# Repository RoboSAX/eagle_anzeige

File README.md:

# eagle_anzeige
Anzeigeelemente für die Masterplatine der Spielfeldsteuerung

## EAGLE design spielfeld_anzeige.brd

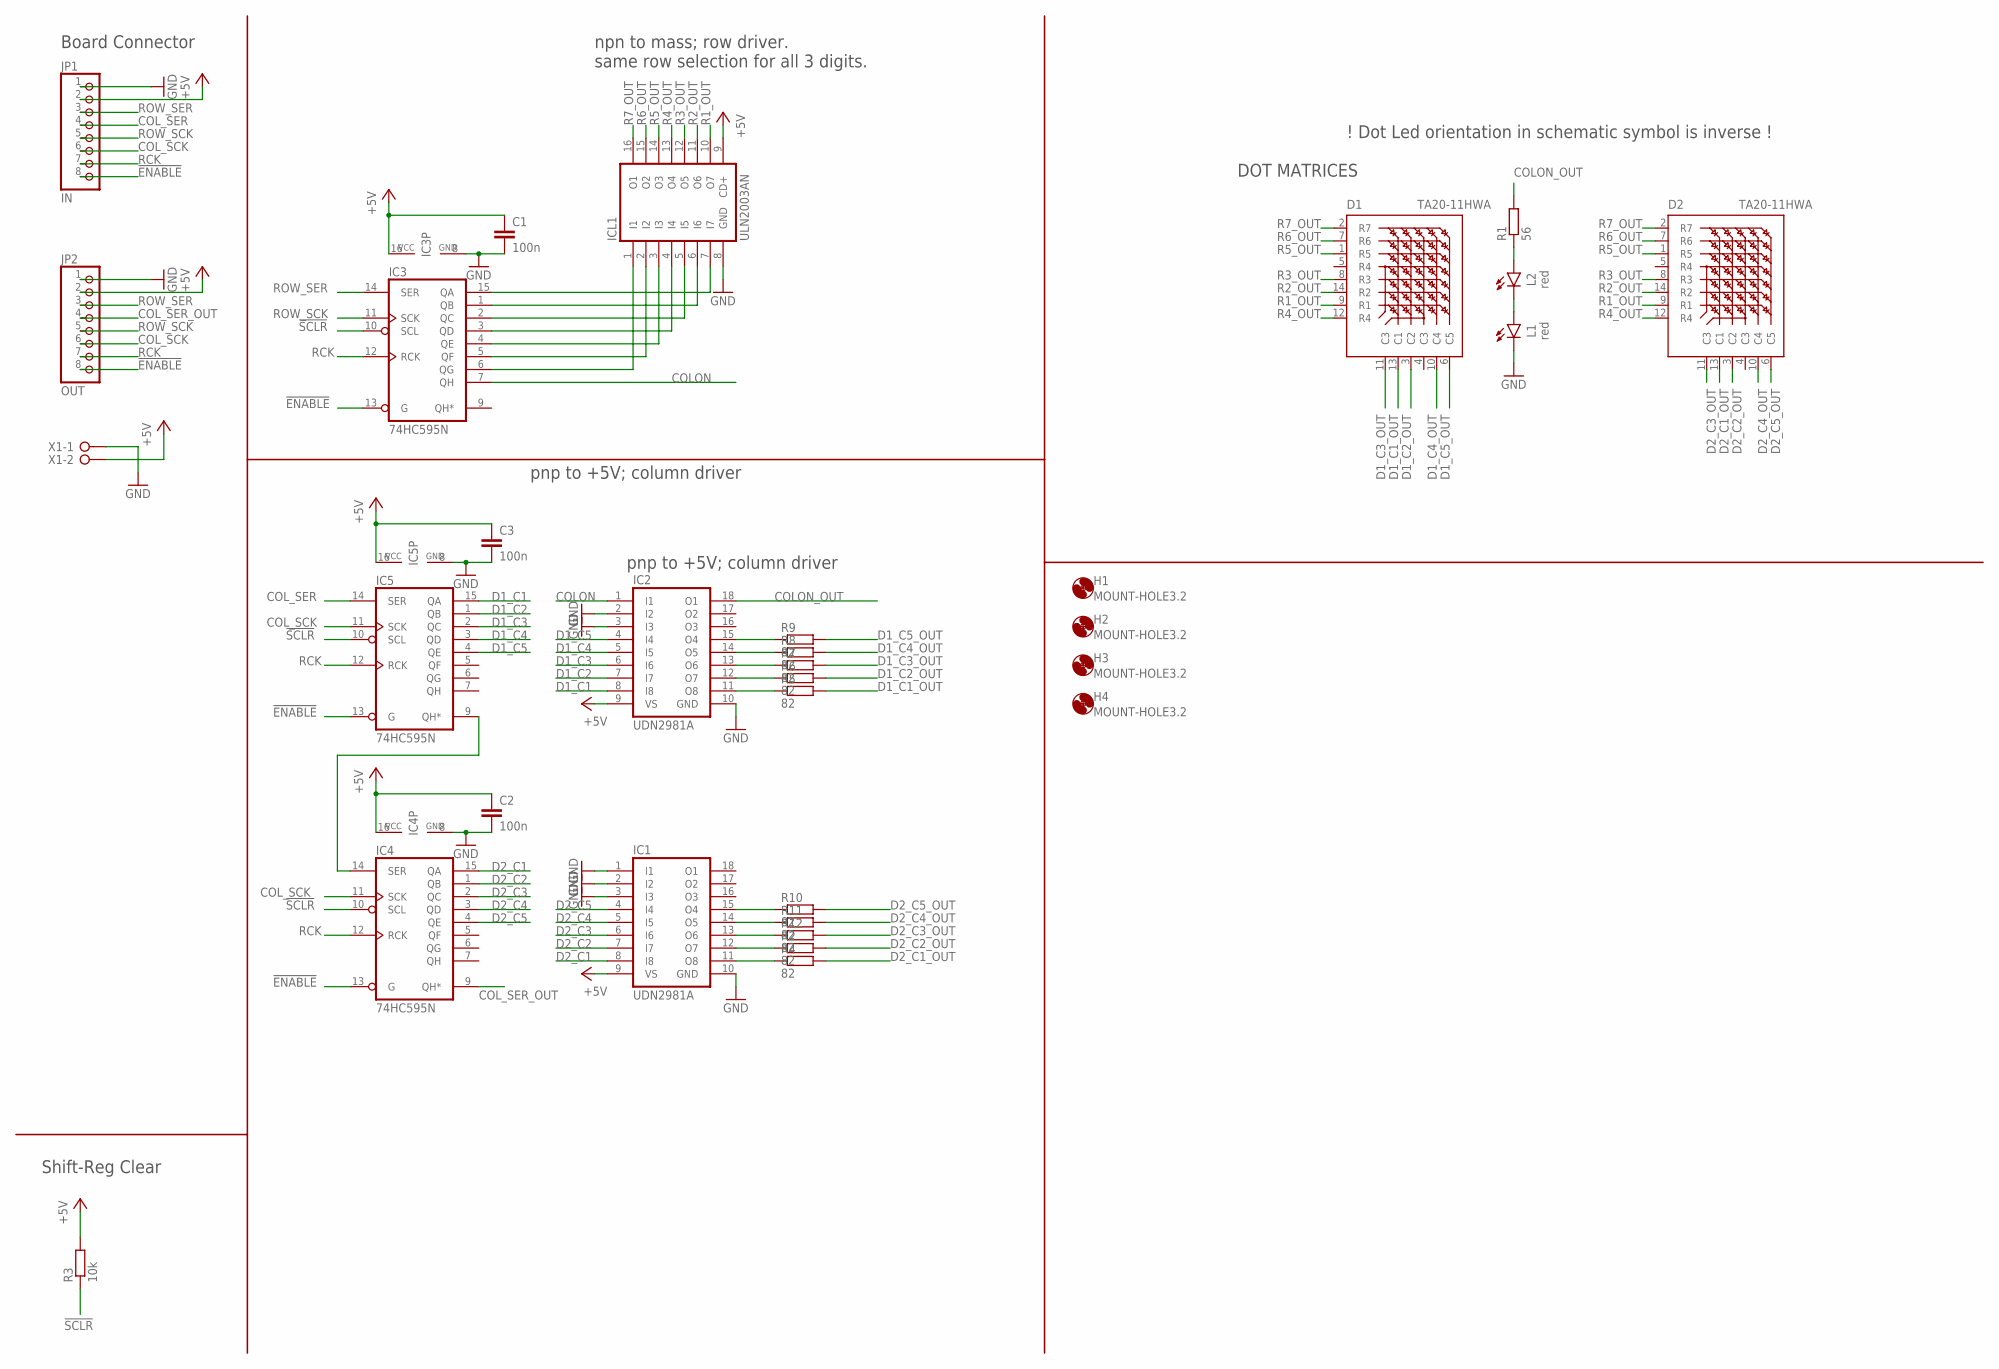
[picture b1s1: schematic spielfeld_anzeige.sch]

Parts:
C1, C2, C3: 100n; C0805
D1, D2: TA20-11HWA
H1, H2, H3, H4: MOUNT-HOLE3.2; 3,2
IC1, IC2: UDN2981A; DIL18
IC3, IC4, IC5: 74HC595N; DIL16
ICL1: ULN2003AN; DIL16
JP1: IN; 1X08
JP2: OUT; 1X08
L1, L2: red; LED_5MM
R1: 56; R3216
R2, R4, R5, R6, R7, R8, R9, R10, R11, R12: 82; R0805
R3: 10k; M3216
X1: W237-02P; W237-132

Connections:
!ENABLE!: IC3.13 (G), IC4.13 (G), IC5.13 (G), JP1.8, JP2.8
!SCLR!: IC3.10 (SCL), IC4.10 (SCL), IC5.10 (SCL), R3.1
+5V: C1.1, C2.1, C3.1, IC1.9 (VS), IC2.9 (VS), IC3.16 (VCC), IC4.16 (VCC), IC5.16 (VCC), ICL1.9 (CD+), JP1.2, JP2.2, R3.2, X1.2
COLON: IC2.1 (I1), IC3.7 (QH)
COLON_OUT: IC2.18 (O1), R1.2
COL_SCK: IC4.11 (SCK), IC5.11 (SCK), JP1.6, JP2.6
COL_SER: IC5.14 (SER), JP1.4
COL_SER_OUT: IC4.9 (QH*), JP2.4
D1_C1: IC2.8 (I8), IC5.15 (QA)
D1_C1_OUT: D1.13 (C1), R5.2
D1_C2: IC2.7 (I7), IC5.1 (QB)
D1_C2_OUT: D1.3 (C2), R6.2
D1_C3: IC2.6 (I6), IC5.2 (QC)
D1_C3_OUT: D1.11 (C3), R7.2
D1_C4: IC2.5 (I5), IC5.3 (QD)
D1_C4_OUT: D1.10 (C4), R8.2
D1_C5: IC2.4 (I4), IC5.4 (QE)
D1_C5_OUT: D1.6 (C5), R9.2
D2_C1: IC1.8 (I8), IC4.15 (QA)
D2_C1_OUT: D2.13 (C1), R4.2
D2_C2: IC1.7 (I7), IC4.1 (QB)
D2_C2_OUT: D2.3 (C2), R2.2
D2_C3: IC1.6 (I6), IC4.2 (QC)
D2_C3_OUT: D2.11 (C3), R12.2
D2_C4: IC1.5 (I5), IC4.3 (QD)
D2_C4_OUT: D2.10 (C4), R11.2
D2_C5: IC1.4 (I4), IC4.4 (QE)
D2_C5_OUT: D2.6 (C5), R10.2
GND: C1.2, C2.2, C3.2, IC1.1 (I1), IC1.2 (I2), IC1.3 (I3), IC1.10 (GND), IC2.2 (I2), IC2.3 (I3), IC2.10 (GND), IC3.8 (GND), IC4.8 (GND), IC5.8 (GND), ICL1.8 (GND), JP1.1, JP2.1, L1.K (C), X1.1
unnamed: L1.A, L2.K (C)
unnamed: IC2.11 (O8), R5.1
unnamed: IC2.12 (O7), R6.1
unnamed: IC2.13 (O6), R7.1
unnamed: IC2.14 (O5), R8.1
unnamed: IC2.15 (O4), R9.1
unnamed: IC1.15 (O4), R10.1
unnamed: IC3.15 (QA), ICL1.7 (I7)
unnamed: IC3.1 (QB), ICL1.6 (I6)
unnamed: IC3.2 (QC), ICL1.5 (I5)
unnamed: IC3.3 (QD), ICL1.4 (I4)
unnamed: IC3.4 (QE), ICL1.3 (I3)
unnamed: L2.A, R1.1
unnamed: IC1.14 (O5), R11.1
unnamed: IC1.13 (O6), R12.1
unnamed: IC1.12 (O7), R2.1
unnamed: IC1.11 (O8), R4.1
unnamed: IC3.5 (QF), ICL1.2 (I2)
unnamed: IC4.14 (SER), IC5.9 (QH*)
unnamed: IC3.6 (QG), ICL1.1 (I1)
R1_OUT: D1.9 (R1), D2.9 (R1), ICL1.10 (O7)
R2_OUT: D1.14 (R2), D2.14 (R2), ICL1.11 (O6)
R3_OUT: D1.8 (R3), D2.8 (R3), ICL1.12 (O5)
R4_OUT: D1.12 (R4), D2.12 (R4), ICL1.13 (O4)
R5_OUT: D1.1 (R5), D2.1 (R5), ICL1.14 (O3)
R6_OUT: D1.7 (R6), D2.7 (R6), ICL1.15 (O2)
R7_OUT: D1.2 (R7), D2.2 (R7), ICL1.16 (O1)
RCK: IC3.12 (RCK), IC4.12 (RCK), IC5.12 (RCK), JP1.7, JP2.7
ROW_SCK: IC3.11 (SCK), JP1.5, JP2.5
ROW_SER: IC3.14 (SER), JP1.3, JP2.3

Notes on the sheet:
npn to mass; row driver. same row selection for all 3 digits.
pnp to +5V; column driver
! Dot Led orientation in schematic symbol is inverse !
DOT MATRICES
Board Connector
Shift-Reg Clear

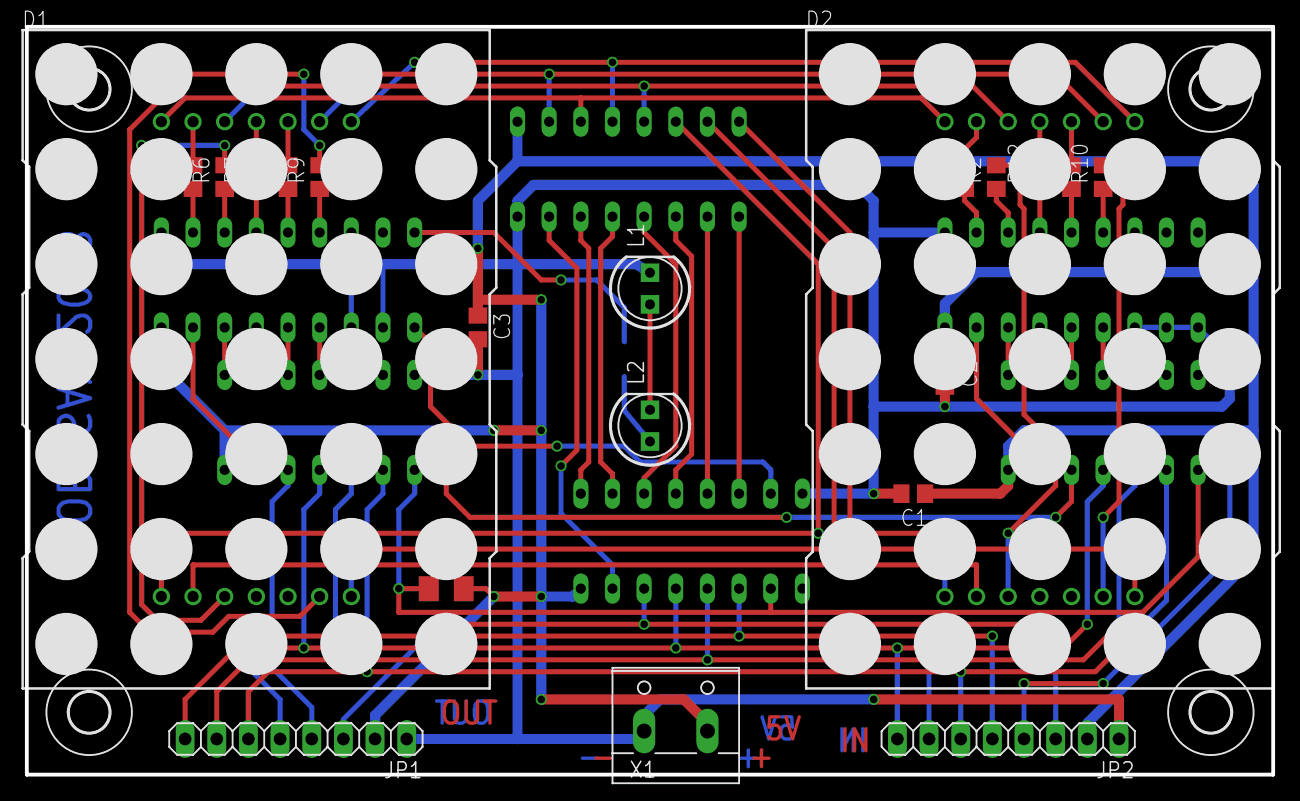
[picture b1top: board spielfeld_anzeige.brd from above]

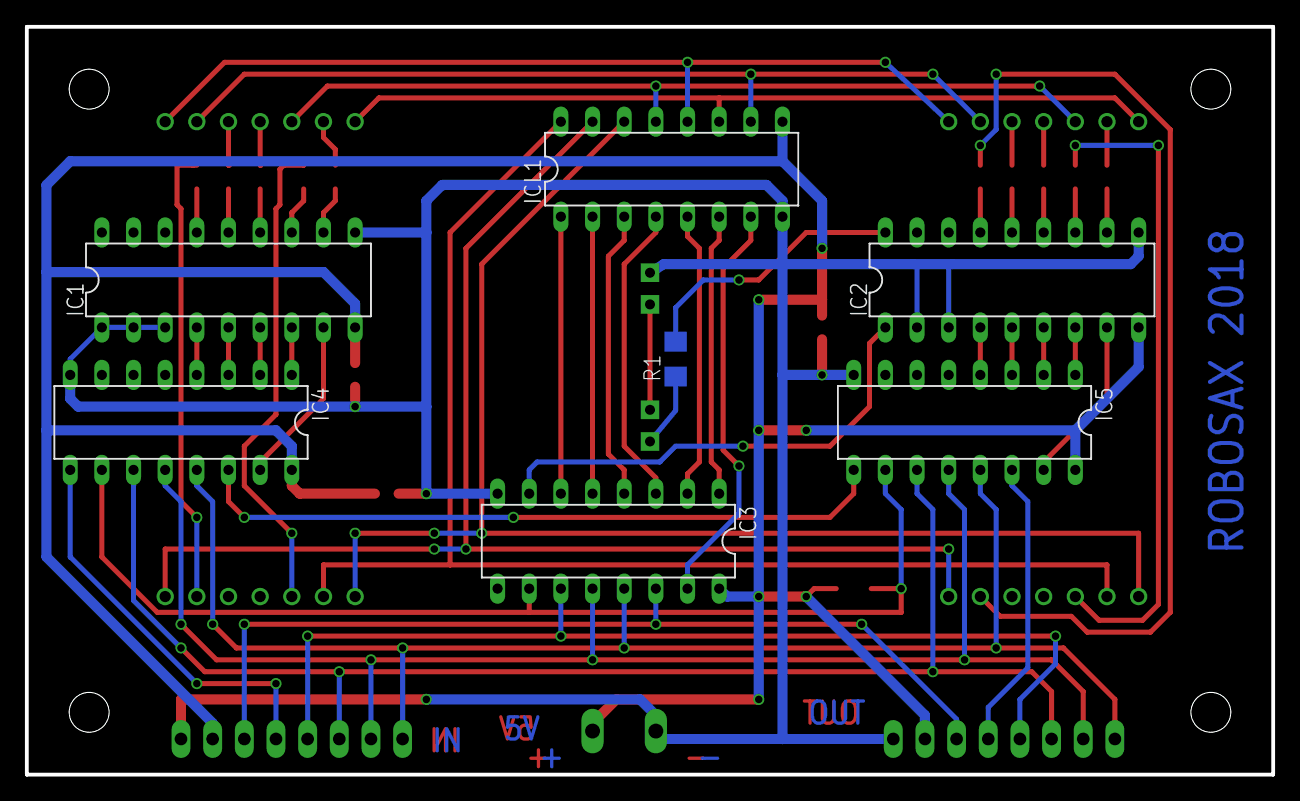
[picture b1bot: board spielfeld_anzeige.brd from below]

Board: 2 copper layers, 100.0 x 60.0 mm, 32 parts (7 on the bottom side), 59 nets.

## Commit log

2018-03-01 inital commit
2018-03-13 Schematic mit 3 Digits fertig
2018-03-13 Reduced to 2 digits on board. Bom updated.
2018-03-18 PCB design finished with tht parts on backside of board
2018-04-27 added measurements to layout added exported images and global pdf
2018-05-09 Revision due to Pete and Leander on 30.04.2018
2018-05-09 Changed Layout (in Progress)
    Updated Eagle-Borad and Schematic
    - Reorganize the outputs of the FFs
    - Move Colon to FF for Rows
    - Change resistors to 0805 and 82 Ohm
    - Put all devices in Layout back to 50 mil grid
    - startet layout from scratch
2018-05-09 Layout fertig
2018-05-15 Doku Update
    BOM and Layout Doku updated
2018-05-15 Documentation Update
2018-05-16 Korrekturen Layout
    LEDs ins mm-Raster zurückgesetzt.
    Maßangaben korrigiert.
    Die freien Eingänge der Treiber-ICs mit GND verbunden.
2018-05-18 moved exported images (circuit, layout) to "export/images/"
2018-05-18 minor bugfixes
2018-05-18 adde files for elecrow
2018-05-18 changed structure of directories
